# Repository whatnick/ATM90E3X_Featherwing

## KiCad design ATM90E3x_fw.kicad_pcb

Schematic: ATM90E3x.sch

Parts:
C1, C2, C3, C4, C5, C6, C7, C8, C9, C10, C11, C12, C14, C15, C16, C17, C19, C20, C21: C_Small; C_0603
C13, C18: C_Small; C_0805
D1, D2, D3, D4: LED; LED_0603
IC1: ATM90E36_ATM90E36; TQFP-48_7x7mm_Pitch0.5mm
J1: CONN_01X04; JST_SH_BM04B-SRSS-TB_04x1.00mm_Straight
J2, J6, J7: GS3
J3, J8: CONN_01X06; JST_SH_BM06B-SRSS-TB_06x1.00mm_Straight
J4: CONN_01X04; PhoenixContact_MC-G_04x3.50mm_Angled
J5: RJ45; RJ45_8
J11: CONN_01X03; JST_SH_BM03B-SRSS-TB_03x1.00mm_Straight
LOGO1: OPEN_HARDWARE_1; OSHW-Logo2_7.3x6mm_SilkScreen
R1, R2, R3, R4, R5, R6, R7, R8, R9, R10, R11, R12, R13, R14, R15, R16, R17, R18, R19, R20, R21, R22, R23, R24, R25, R26: R; R_0603
R27, R28: SMD-RES-ARRAY; R_Array_Concave_4x0603
Y1: Crystal_GND24; Crystal_SMD_2520-4pin_2.5x2.0mm

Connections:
CF1: IC1.25, J1.4, R28.4
CF2: IC1.26, J1.3, R28.3
CF3: IC1.27, J1.2, R28.2
CF4: IC1.28, J1.1, R28.1
CS: IC1.37, J3.5, R27.8; also elsewhere on the board
DMA: IC1.36, J2.2, J8.1
GND: C1.2, C2.1, C3.2, C4.1, C5.2, C6.2, C7.2, C8.1, C9.2, C10.1, C11.2, C12.2, C13.1, C14.1, C15.1, C16.1, C17.2, C18.2, C19.2, C20.1, C21.1, D1.1, D2.1, D3.1, D4.1, IC1.2, IC1.12, IC1.19, IC1.32, IC1.44, IC1.47, J2.1, J3.6, J4.1, J6.1, J7.1, R1.1, R2.2, R3.1, R4.2, R10.2, R12.2, R13.1, R14.2, R15.1, R16.2, R22.2, R23.2, R24.2, R26.2, Y1.2, Y1.4; also elsewhere on the board
I1N: C2.2, IC1.4, R6.1
I1N_IN: J5.2, R2.1, R6.2
I1P: C1.1, IC1.3, R5.1
I1P_IN: J5.1, R1.2, R5.2
I2N: C8.2, IC1.6, R18.1
I2N_IN: J5.4, R14.1, R18.2
I2P: C7.1, IC1.5, R17.1
I2P_IN: J5.3, R13.2, R17.2
I3N: C4.2, IC1.8, R8.1
I3N_IN: J5.6, R4.1, R8.2
I3P: C3.1, IC1.7, R7.1
I3P_IN: J5.5, R3.2, R7.2
IN: C10.2, IC1.10, R20.1
IN_IN: J5.8, R16.1, R20.2
IP: C9.1, IC1.9, R19.1
IP_IN: J5.7, R15.2, R19.2
IRQ1: IC1.31, J8.4
IRQ2: IC1.30, J8.5
MISO: IC1.39, J3.3, R27.6; also elsewhere on the board
MOSI: IC1.40, J3.2, R27.5; also elsewhere on the board
unnamed: C13.2, C14.2, IC1.11
unnamed: C15.2, IC1.14, R23.1
unnamed: C17.1, C18.1, IC1.42, IC1.43
unnamed: C19.1, IC1.41, R25.2
unnamed: C20.2, IC1.16, R24.1
unnamed: C21.2, IC1.18, R26.1
unnamed: D1.2, R28.8
unnamed: D2.2, R28.7
unnamed: D3.2, R28.6
unnamed: D4.2, R28.5
unnamed: IC1.20, Y1.1
unnamed: IC1.21, Y1.3
PM0: IC1.33, J6.2, J8.3
PM1: IC1.34, J7.2, J8.2
SCLK: IC1.38, J3.4, R27.7; also elsewhere on the board
UA: J4.4, R9.1; also elsewhere on the board
UB: J4.3, R11.1; also elsewhere on the board
UC: J4.2, R21.1; also elsewhere on the board
V1P: C11.1, IC1.13, R21.2, R22.1
V2P: C6.1, IC1.15, R11.2, R12.1
V3P: C5.1, IC1.17, R9.2, R10.1
VDD: C12.1, C16.2, IC1.1, IC1.48, J2.3, J3.1, J6.3, J7.3, R25.1, R27.1, R27.2, R27.3, R27.4; also elsewhere on the board
WARN: IC1.29, J8.6
ZX0: IC1.22, J11.3
ZX1: IC1.23, J11.2
ZX2: IC1.24, J11.1

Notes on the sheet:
Voltage Sampling
Current Sampling
Digital and Analog I/O connectors
ATM90E3X Poly Phase Metering AFE
Optional Neutral CT

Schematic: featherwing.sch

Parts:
C22: 1u/16V; C_0603
C23: 100u/16V; CP_Elec_5x5.8
C24: 1u/50V; C_0603
C25: 220u/50V; CP_Elec_8x10
D5: LED; LED_0603
D6: D_Schottky; D_SOD-123
D7, D8, D9: D_Schottky; D_SMA
J9: GS3
J10: GROVE-SMD-90D; SEEED-CONNECTOR--2016_HW4-SMD-2.0-90D
JP1: Jumper_NC_Small; GS2
LOGO2: LOGO; Whatnick_logo
MS1: ADAFRUIT_FEATHERWING
R29: R; R_0603_HandSoldering
U1: ROF-78E; SMD-4

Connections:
/Featherwing/VIN: C24.1, C25.1, D7.1, D8.1, D9.1, U1.1
/Featherwing/VOUT: C22.1, C23.1, D6.2, JP1.2, U1.3
CS: J9.1 (G1), J9.2 (G2), MS1.22; also elsewhere on the board
GND: C22.2, C23.2, C24.2, C25.2, D5.1, J10.4, J10.SS1, J10.SS2, MS1.4, U1.2; also elsewhere on the board
MISO: MS1.13; also elsewhere on the board
MOSI: MS1.12; also elsewhere on the board
unnamed: D5.2, R29.2
unnamed: J9.3 (G3), MS1.21
unnamed: J10.1, MS1.18
unnamed: J10.2, MS1.17
unnamed: JP1.1, R29.1
SCLK: MS1.11; also elsewhere on the board
UA: D7.2; also elsewhere on the board
UB: D8.2; also elsewhere on the board
UC: D9.2; also elsewhere on the board
USB: D6.1, MS1.26
VDD: J10.3, MS1.2; also elsewhere on the board

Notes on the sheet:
Rectifier and Regulator
Feather Connector

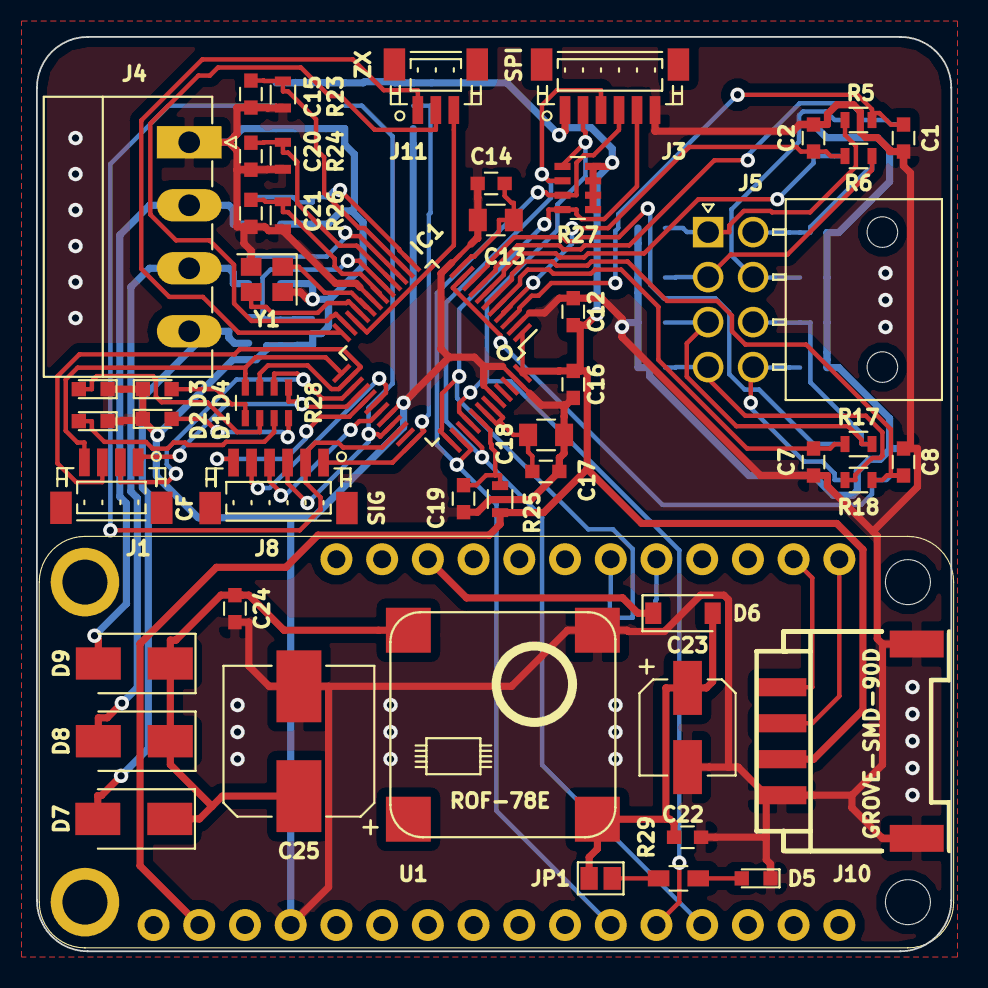
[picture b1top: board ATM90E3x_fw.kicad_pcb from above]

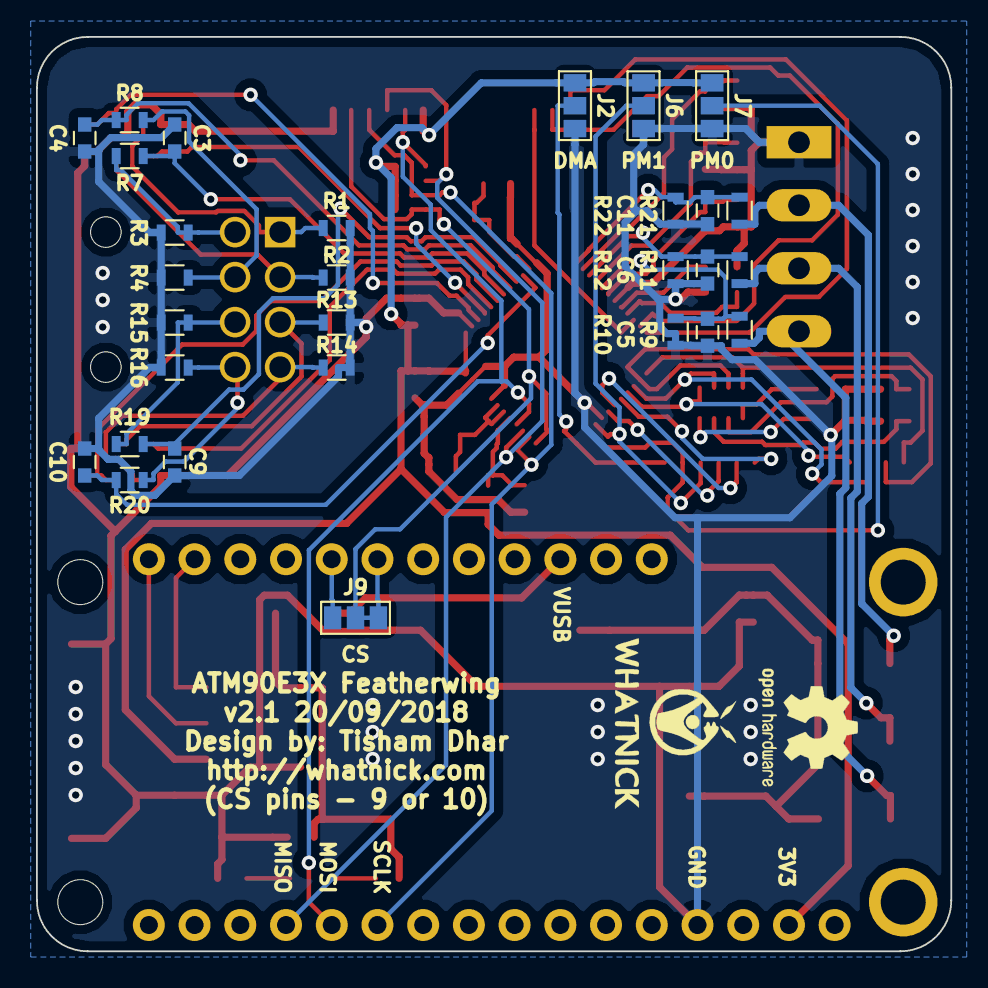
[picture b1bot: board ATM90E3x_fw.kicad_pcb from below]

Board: 2 copper layers, 50.8 x 50.8 mm, 81 parts (31 on the bottom side), 61 nets.

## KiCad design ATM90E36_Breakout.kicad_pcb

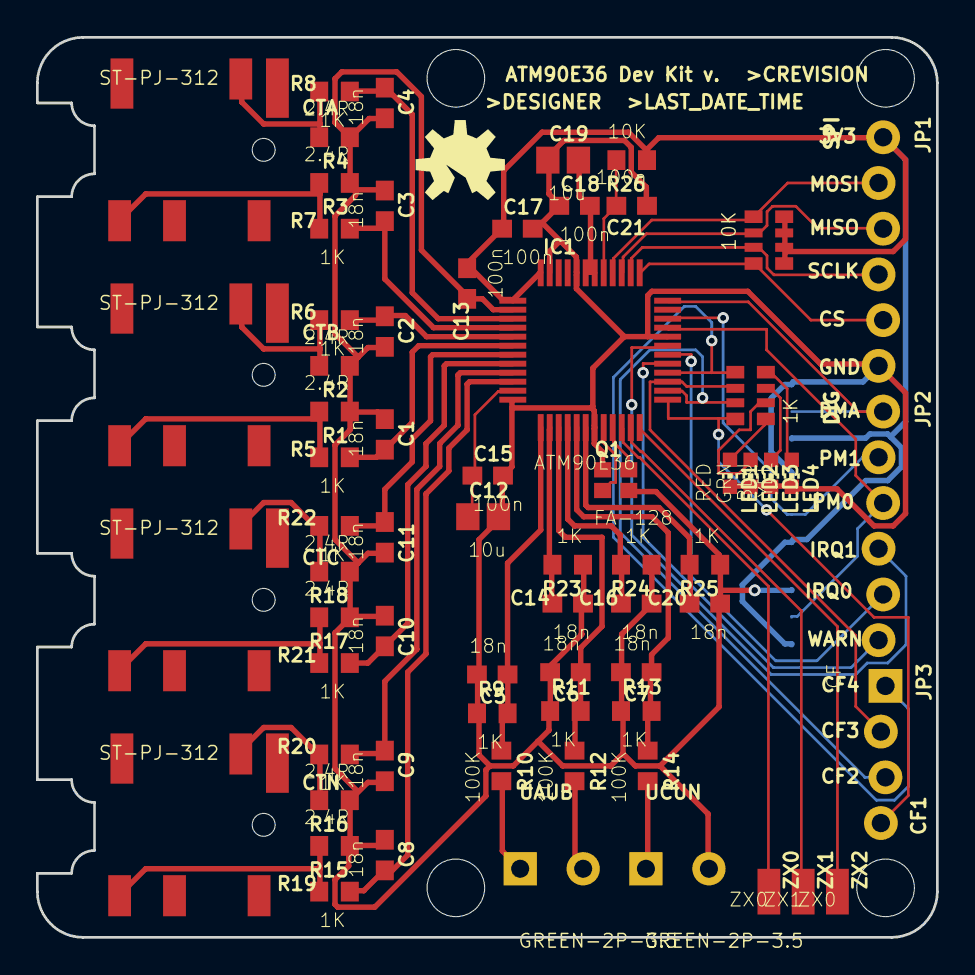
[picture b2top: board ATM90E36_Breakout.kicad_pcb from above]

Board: 2 copper layers, 50.0 x 50.0 mm, 75 parts (0 on the bottom side), 53 nets.

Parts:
@HOLE0, @HOLE1, @HOLE2, @HOLE3: (no value)
C1, C2, C3, C4, C5, C6, C7, C8, C9, C10, C11, C14, C16, C20: 18n; C0603
C12, C19: 10u; C0805
C13, C15, C17, C18, C21: 100n; C0603
CTA: ST-PJ-312; AUDIO6P-SMD-3.5-14.0X6.4X5.0MM
CTB: ST-PJ-312; AUDIO6P-SMD-3.5-14.0X6.4X5.0MM
CTC: ST-PJ-312; AUDIO6P-SMD-3.5-14.0X6.4X5.0MM
CTN: ST-PJ-312; AUDIO6P-SMD-3.5-14.0X6.4X5.0MM
DMA: JUMPER-PAD-3-NOFULL_BOX_SILK; PAD-JUMPER-3-NO_YES_SILK_FULL_BOX
IC1: ATM90E36; TQFP48
JP1: SPI; 1X06_LOCK
JP2: DIG; 1X06_LOCK
JP3: CF; 1X04_LOCK
LED1: RED; CHIP-LED0603
LED2: GRN; CHIP-LED0603
LED3: BLU; CHIP-LED0603
LED4: YEL; CHIP-LED0603
LOGO1: OSHW-LOGOM; OSHW-LOGO-M
PM0, PM1: JUMPER-PAD-3-NOFULL_BOX_SILK; PAD-JUMPER-3-NO_YES_SILK_FULL_BOX
Q1: FA-128
R1, R2, R3, R4, R15, R16, R17, R18: 2.4R; R0603
R5, R6, R7, R8, R9, R11, R13, R19, R20, R21, R22, R23, R24, R25: 1K; R0603
R10, R12, R14: 100K; R0603
R26: 10K; R0603
R27: 1K; RA1206-8
R36: 10K; RA1206-8
UAUB: GREEN-2P-3.5; H2-3.5-7.0X7.0MM
UCUN: GREEN-2P-3.5; H2-3.5-7.0X7.0MM
ZX0, ZX2: ZX0; SMD1,27-2,54
ZX1: ZX1; SMD1,27-2,54

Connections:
!CS: IC1.37, JP1.5, R36.4
CF1: IC1.25, JP3.4, R27.8
CF2: IC1.26, JP3.3, R27.7
CF3: IC1.27, JP3.2, R27.6
CF4: IC1.28, JP3.1, R27.5
DMA: DMA.2, IC1.36, JP2.1
GND: C1.1, C2.2, C3.1, C4.2, C5.2, C6.2, C7.2, C8.1, C9.2, C10.1, C11.2, C12.2, C13.1, C14.2, C15.2, C16.2, C17.2, C18.1, C19.1, C20.2, C21.1, DMA.3, IC1.2, IC1.12, IC1.19, IC1.32, IC1.44, IC1.47, JP1.6, LED1.C, LED2.C, LED3.C, LED4.C, PM0.3, PM1.3, Q1.2, Q1.4, R1.1, R2.1, R3.1, R4.1, R9.1, R11.1, R13.1, R15.1, R16.1, R17.1, R18.1, R23.1, R24.1, R25.1, UCUN.2
IA+: CTA.L, R4.2, R8.1
IA-: CTA.COM1, R3.2, R7.1
IAN: C3.2, IC1.4, R7.2
IAP: C4.1, IC1.3, R8.2
IB+: CTB.L, R2.2, R6.1
IB-: CTB.COM1, R1.2, R5.1
IBN: C1.2, IC1.6, R5.2
IBP: C2.1, IC1.5, R6.2
IC+: CTC.L, R18.2, R22.1
IC-: CTC.COM1, R17.2, R21.1
ICN: C10.2, IC1.8, R21.2
ICP: C11.1, IC1.7, R22.2
IN+: CTN.L, R16.2, R20.1
IN-: CTN.COM1, R15.2, R19.1
INN: C8.2, IC1.10, R19.2
INP: C9.1, IC1.9, R20.2
IRQ1: IC1.31, JP2.4
IRQ2: IC1.30, JP2.5
MISO: IC1.39, JP1.3, R36.2
MOSI: IC1.40, JP1.2, R36.1
unnamed: C21.2, IC1.41, R26.2
unnamed: LED4.A, R27.4
unnamed: LED3.A, R27.3
unnamed: LED2.A, R27.2
unnamed: LED1.A, R27.1
unnamed: C14.1, IC1.14, R23.2
unnamed: IC1.20, Q1.1
unnamed: C16.1, IC1.16, R24.2
unnamed: C20.1, IC1.18, R25.2
unnamed: IC1.21, Q1.3
unnamed: C18.2, C19.2, IC1.42, IC1.43
unnamed: C12.1, C15.1, IC1.11
PM0: IC1.33, JP2.3, PM0.2
PM1: IC1.34, JP2.2, PM1.2
SCLK: IC1.38, JP1.4, R36.3
UA: R10.2, UAUB.1
UB: R12.2, UAUB.2
UC: R14.2, UCUN.1
VAP: C5.1, IC1.13, R9.2, R10.1
VBP: C6.1, IC1.15, R11.2, R12.1
VCP: C7.1, IC1.17, R13.2, R14.1
VDD: C13.2, C17.1, DMA.1, IC1.1, IC1.48, JP1.1, PM0.1, PM1.1, R26.1, R36.5, R36.6, R36.7, R36.8
WARN: IC1.29, JP2.6
ZX0: IC1.22, ZX0.1
ZX1: IC1.23, ZX1.1
ZX2: IC1.24, ZX2.1

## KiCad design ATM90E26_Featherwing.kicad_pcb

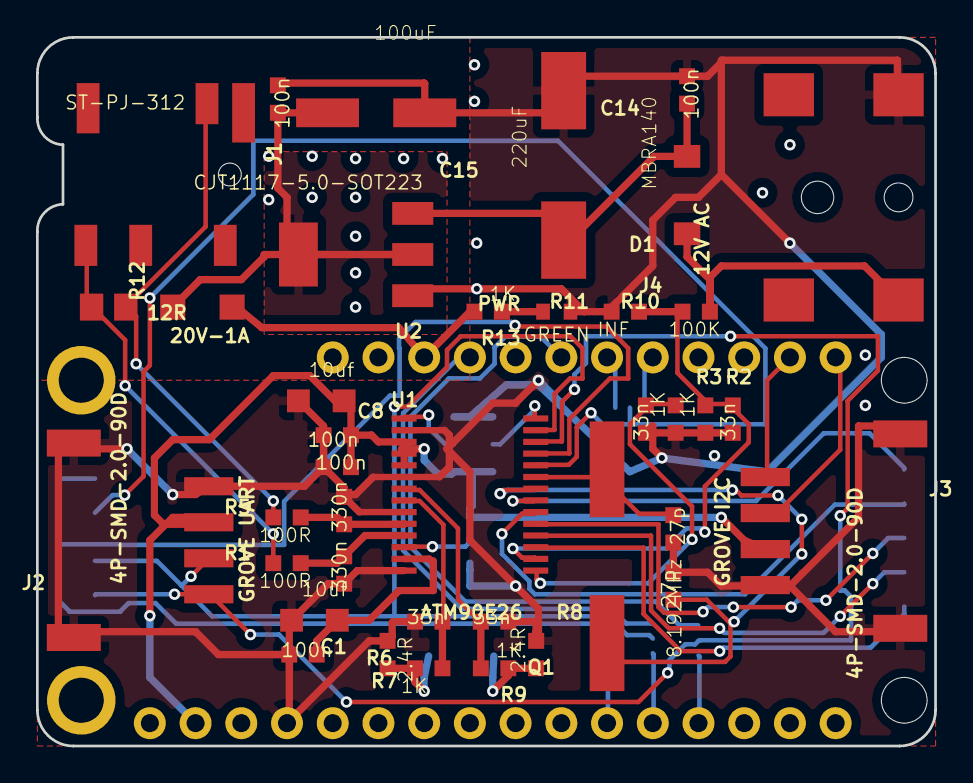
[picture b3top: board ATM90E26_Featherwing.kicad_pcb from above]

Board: 2 copper layers, 49.9 x 39.4 mm, 59 parts (0 on the bottom side), 41 nets.

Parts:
C1, C8: 10uf; AVX-A
C2, C6, C9, C16, C17: 100n; C0603
C3, C7: 330n; C0603
C4, C5, C10, C13: 33n; C0603
C11, C12: 27p; C0603
C14: 220uF; 140CLH-1010
C15: 100uF; 153CLV-0605
CF1, CF2: WIREPADSMD1,27-254; SMD1,27-2,54
CS: WIREPADSMD1,27-254; SMD1,27-2,54
CSMUX: JUMPER-PAD-3-NOYES_SILK; PAD-JUMPER-3-NO_YES_SILK
D1: MBRA140; SMA-DIODE
D2: 20V-1A; SOD-123
I2N_IN, I2P_IN: WIREPADSMD1,27-254; SMD1,27-2,54
INT: WIREPADSMD1,27-254; SMD1,27-2,54
J1: ST-PJ-312; AUDIO6P-SMD-3.5-14.0X6.4X5.0MM
J2, J3: 4P-SMD-2.0-90D; HW4-SMD-2.0-90D
J4: 12V AC; DC_BARREL_JACK_SMD_2MM
LOGO1: OSHW-LOGOM; OSHW-LOGO-M
MMD0, MMD1: JUMPER-PAD-3-NOFULL_BOX_SILK; PAD-JUMPER-3-NO_YES_SILK_FULL_BOX
MS1: FEATHERWING_NODIM; FEATHERWING_DIM
PWR: GREEN; LED-0603
Q1: 8.192MHz; HC49UP
R1, R5: 100R; R0603
R2, R3, R6, R9, R13: 1K; R0603
R7, R8: 2.4R; R0603
R10: 100K; R0603
R11: INF; R0603
R12: 12R; 0805
RXMUX: JUMPER-PAD-3-NOYES_SILK; PAD-JUMPER-3-NO_YES_SILK
SCKMUX: JUMPER-PAD-2-NOYES_SILK; PAD-JUMPER-2-NO_YES_SILK
SCLK: WIREPADSMD1,27-254; SMD1,27-2,54
SI/RX: WIREPADSMD1,27-254; SMD1,27-2,54
SO/TX: WIREPADSMD1,27-254; SMD1,27-2,54
TXMUX: JUMPER-PAD-3-NOYES_SILK; PAD-JUMPER-3-NO_YES_SILK
U1: ATM90E26; SSOP-28
U2: CJT1117-5.0-SOT223; SOT-223
USEL: JUMPER-PAD-3-NOFULL_BOX_SILK; PAD-JUMPER-3-NO_YES_SILK_FULL_BOX
WARN: WIREPADSMD1,27-254; SMD1,27-2,54
ZX: WIREPADSMD1,27-254; SMD1,27-2,54

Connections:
+3V3: C6.2, C8.+, C9.1, J2.3, J3.3, MMD0.3, MMD1.1, MS1.2, U1.3, U1.4, U1.5, USEL.3
ATM_RX: MS1.25, RXMUX.3
ATM_TX: MS1.23, TXMUX.3
CLKIN: C11.1, Q1.1, U1.22
CLKOUT: C12.1, Q1.2, U1.23
CS: CS.1, CSMUX.2, U1.24
CS_9: CSMUX.1, MS1.21
CS_10: CSMUX.3, MS1.22
GND: C1.-, C2.1, C3.1, C4.1, C5.1, C6.1, C7.2, C8.-, C9.2, C10.1, C11.2, C12.2, C13.2, C14.-, C15.-, C16.1, C17.1, J2.4, J2.SS1, J2.SS2, J3.4, J3.SS1, J3.SS2, J4.P2, MMD0.1, MMD1.3, MS1.4, PWR.-, R2.1, R3.1, R7.1, R8.2, R11.2, U1.2, U1.6, U1.9, U1.14, U2.1, USEL.1
I1N: C7.1, R5.1, U1.10
I1N_IN: J1.L, R5.2, R12.2
I1P: C3.2, R1.1, U1.11
I1P_IN: J1.COM1, R1.2, R12.1
I2N: C10.2, R6.1, U1.8
I2N_IN: I2N_IN.1, R6.2, R7.2
I2P: C13.1, R9.1, U1.7
I2P_IN: I2P_IN.1, R8.1, R9.2
MISO: MS1.13, TXMUX.1
MOSI: MS1.12, RXMUX.1
unnamed: MMD1.2, U1.1
unnamed: MMD0.2, U1.28
unnamed: D1.A, J4.P1@2, R10.1
unnamed: C14.+, C16.2, D1.C, U2.3
unnamed: PWR.+, R13.2
unnamed: CF1.1, U1.18
unnamed: CF2.1, U1.19
unnamed: U1.12, USEL.2
unnamed: U1.21, ZX.1
unnamed: INT.1, U1.20
unnamed: U1.17, WARN.1
SCK: MS1.11, SCKMUX.1
SCL: J3.1, MS1.18
SCLK: SCKMUX.2, SCLK.1, U1.25
SDA: J3.2, MS1.17
SI/RX: J2.2, RXMUX.2, SI/RX.1, U1.27
SO/TX: J2.1, SO/TX.1, TXMUX.2, U1.26
USB: D2.-, MS1.26, R13.1
VN: C5.2, R3.2, U1.15
VP: C4.2, R2.2, R10.2, R11.1, U1.16
VREF: C1.+, C2.2, U1.13
V_OUT: C15.+, C17.2, D2.+, U2.2, U2.TER

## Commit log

2017-06-19 Initial import
2017-06-22 Arrange parts
2017-07-08 Changes from freelancer on fiverr
2017-07-11 Updates from urbito, wired up featherwing
2017-07-18 Urbito delivery
2017-07-18 Urbito delivery gnd plane fix
2017-07-28 Updated master layout
2017-07-28 Playing with autoplace
2017-07-29 Continuing place
2017-07-29 Place progress
2017-07-29 Place completed
2017-07-30 Fixed global names after ERC
2017-07-30 Partial autoroute
2017-07-30 Complete autoroute
2017-07-30 And bottom ground place
2017-07-30 Neaten up silkscreen
2017-07-31 Create gerbers
2018-05-28 Reroute to kicad nightly
2018-05-29 New gerbers
2018-05-29 Consolidate gerbers
2018-09-20 Update gerbers and add default chip select
2018-09-20 Add values for additional parts
2018-09-21 Update parts
2019-12-04 New BOM files
